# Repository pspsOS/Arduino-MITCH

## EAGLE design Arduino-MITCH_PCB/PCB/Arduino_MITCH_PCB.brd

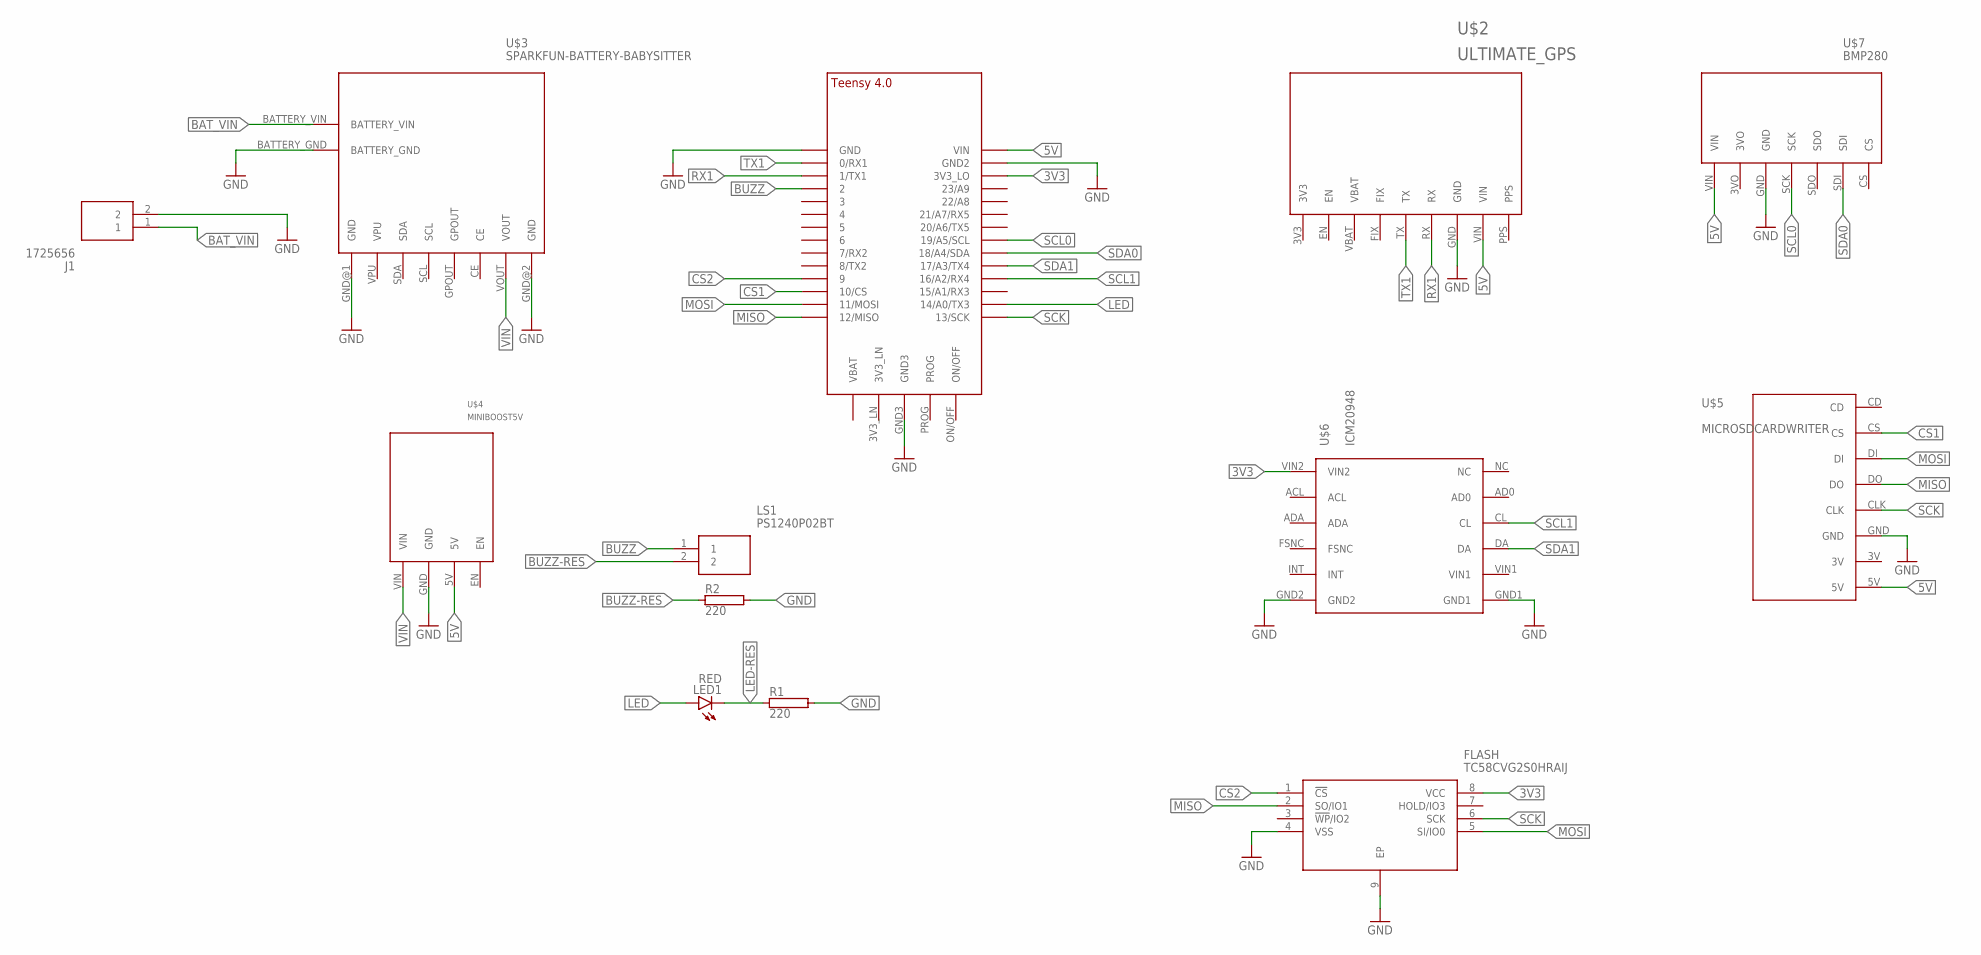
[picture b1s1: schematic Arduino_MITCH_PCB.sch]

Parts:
FLASH: TC58CVG2S0HRAIJ; SON127P800X600X80-9N
J1: 1725656
LED1: RED; LED5MM
LS1: PS1240P02BT
R1, R2: 220; HPS58
U$1: TEENSY_4.0-BASIC
U$2: ULTIMATE_GPS
U$3: SPARKFUN-BATTERY-BABYSITTER
U$4: MINIBOOST5V
U$5: MICROSDCARDWRITER
U$6: ICM20948
U$7: BMP280

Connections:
3V3: FLASH.8 (VCC), U$1.3V3_LO, U$6.VIN2
5V: U$1.VIN, U$2.VIN, U$4.5V, U$5.5V, U$7.VIN
BAT_VIN: J1.1, U$3.BATTERY_VIN
BUZZ: LS1.1, U$1.2
BUZZ-RES: LS1.2, R2.1
CS1: U$1.10/CS, U$5.CS
CS2: FLASH.1 (!CS), U$1.9/CS (9)
GND: FLASH.4 (VSS), FLASH.9 (EP), J1.2, R1.2, R2.2, U$1.GND, U$1.GND2, U$1.GND3, U$2.GND, U$3.BATTERY_GND, U$3.GND@1 (GND), U$3.GND@2 (GND), U$4.GND, U$5.GND, U$6.GND1, U$6.GND2, U$7.GND
LED: LED1.A, U$1.14/A0 (14/A0/TX3)
LED-RES: LED1.K (C), R1.1
MISO: FLASH.2 (SO/IO1), U$1.12/MISO, U$5.DO
MOSI: FLASH.5 (SI/IO0), U$1.11/MOSI, U$5.DI
RX1: U$1.1/TX (1/TX1), U$2.RX
SCK: FLASH.6 (SCK), U$1.13/SCK, U$5.CLK
SCL0: U$1.19/A5/SCL, U$7.SCK
SCL1: U$1.16/A2 (16/A2/RX4), U$6.CL
SDA0: U$1.18/A4/SDA, U$7.SDI
SDA1: U$1.17/A3 (17/A3/TX4), U$6.DA
TX1: U$1.0/RX (0/RX1), U$2.TX
VIN: U$3.VOUT, U$4.VIN

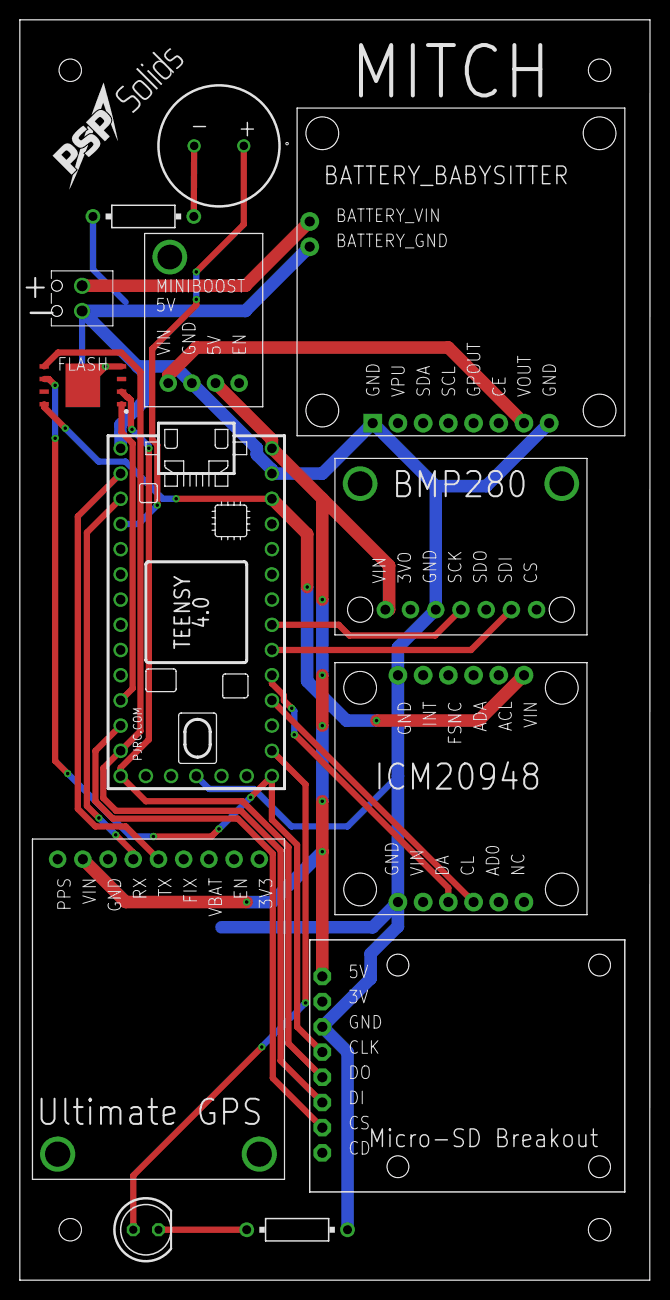
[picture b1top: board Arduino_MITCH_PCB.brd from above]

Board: 2 copper layers, 63.5 x 127.0 mm, 13 parts (0 on the bottom side), 20 nets.

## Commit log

2021-05-25 Started GPS Teensy Code
2021-05-26 Transferred IMU code
2021-05-26 Continued transferring the code over
2021-05-29 Got BMP and IMU sensors working with Teensy
2021-05-30 Debugged code with MITCH hardware
2021-05-30 Added Libraries folder for reference
2021-06-04 Added Eagle Library
2021-06-04 Finalized Library and Parts List
2021-06-04 Renamed Libraries for less confusion
2021-06-11 Completed Schematic
2021-06-11 began PCB, updated cs pin
2021-06-13 1st draft of pcb
2021-06-19 Added a piezo buzzer to PCB
2021-06-19 Added LED for debugging and custom images
2021-06-19 Updated Parts list
2021-06-19 Updated Eagle Library
2021-06-20 Fixed minor errors
2021-06-23 Fixed Flash, added GND plane
2021-06-23 Reshaped GND plane and completed drc
2021-07-13 Mark B's NAND code
2021-07-15 Teensy SPI library implemented
2021-07-28 Changed file naming and fixed errors originating from the interface file
    Changed .c to .cpp
    added PSPHA prefix to heavily modified SPI files
2021-07-30 Added comments and changed what is read from chip
    Follow commented instructions to test code.
    Expect the print function to return 56
2021-09-04 Updated Buzzer and LED
2021-09-11 Fixed GPS lock issue
